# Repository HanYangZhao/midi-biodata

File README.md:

# MIDI Biodata Sonification Device

This repository was built upon code from https://github.com/electricityforprogress/BiodataFeather

Here you find the hardware and enclosure design files for the MIDI Biodata Sonification Devices

- enclosures: contains FreeCAD design and STL files for the enclosure
- firmware: 
  - MIDI_Psychogalv_328p_v021: unmodified firmware from electricityforprogress/MIDIsprout
  - arduino-nano: firmware for MIDI Biodata Sonification Device by me. This firmware offers the following new features over original version
    - Instead of menus, we use a web page to configure the device. The webpage uses webserial to send a json config to the board.
    - Allow all 7 modes of the major scale to be selected. I'm also included the chromatic and Raga Bhairav scale.
    - Selectable root note
    - Chord drone with selectable bpm and frequency. The chord is a triad based on the scale chosen.
    - Refactored code into multipe files for easier understanding.
    - Remove menu codes to save space, some optimization to free up the stack.
  - esp32: Same as main but for ESP32, the arduino-LEDFader folder needs to be copied to .../Arduino/Libraries. This firmware offer the additional:
    - 12 presets can be configured, each preset contains its own scale and root note, and can be triggered via MIDI CC/PC/NOTE
    - BLE MIDI support
- kicad: hardware design as KiCAD project and Gerber files. The board is designed to be used add-on to any microcontroller but also has footprint for the esp32s3 supermini board.

The hardware design and firmware is based on the work of electricityforprogress and thus licensed under the MIT license.

The enclosure design is however licensed under CC0 (public domain), except for the logo which is under copyright of [DipthDesign](https://www.dipth.de). For private use, anyone is free to print the enclosure with logo and without permission.

## Installation 

### Arduino nano

Download https://github.com/jgillick/arduino-LEDFader/tree/master to .../Arduino/Libraries

### ESP32

* Copy ./firmware/esp32/arduino-LEDFader to .../Arduino/Libraries
* Install arduino tiny usb library
* Device mode only support S2/S3/P4 and additional Tools menu are needed
    USB Mode=USB-OTG (TinyUSB) for S3 and P4
    USB CDC On Boot=Enabled, USB Firmware MSC On Boot=Disabled, USB DFU On Boot=Disabled
* BLE MIDI only works on ESP32-S3

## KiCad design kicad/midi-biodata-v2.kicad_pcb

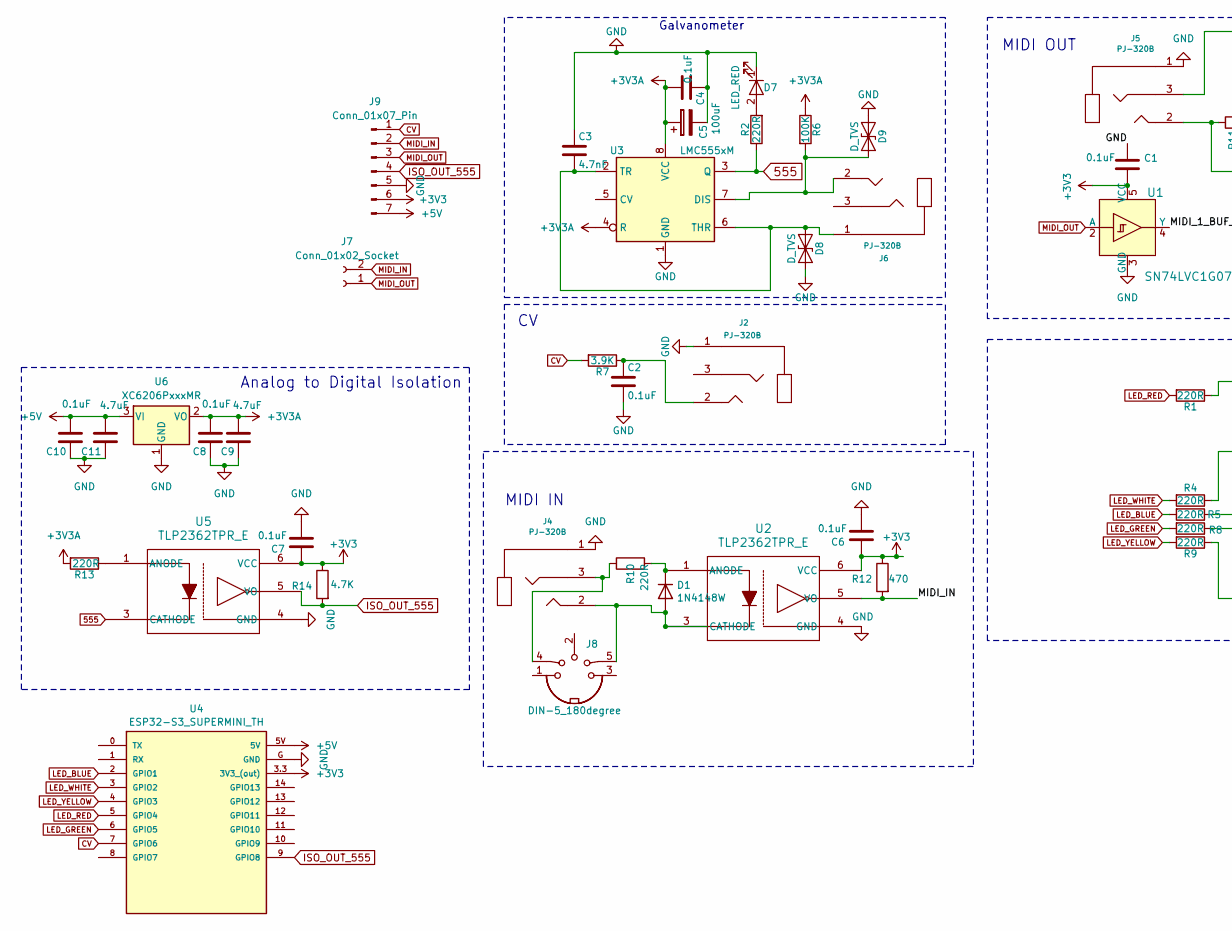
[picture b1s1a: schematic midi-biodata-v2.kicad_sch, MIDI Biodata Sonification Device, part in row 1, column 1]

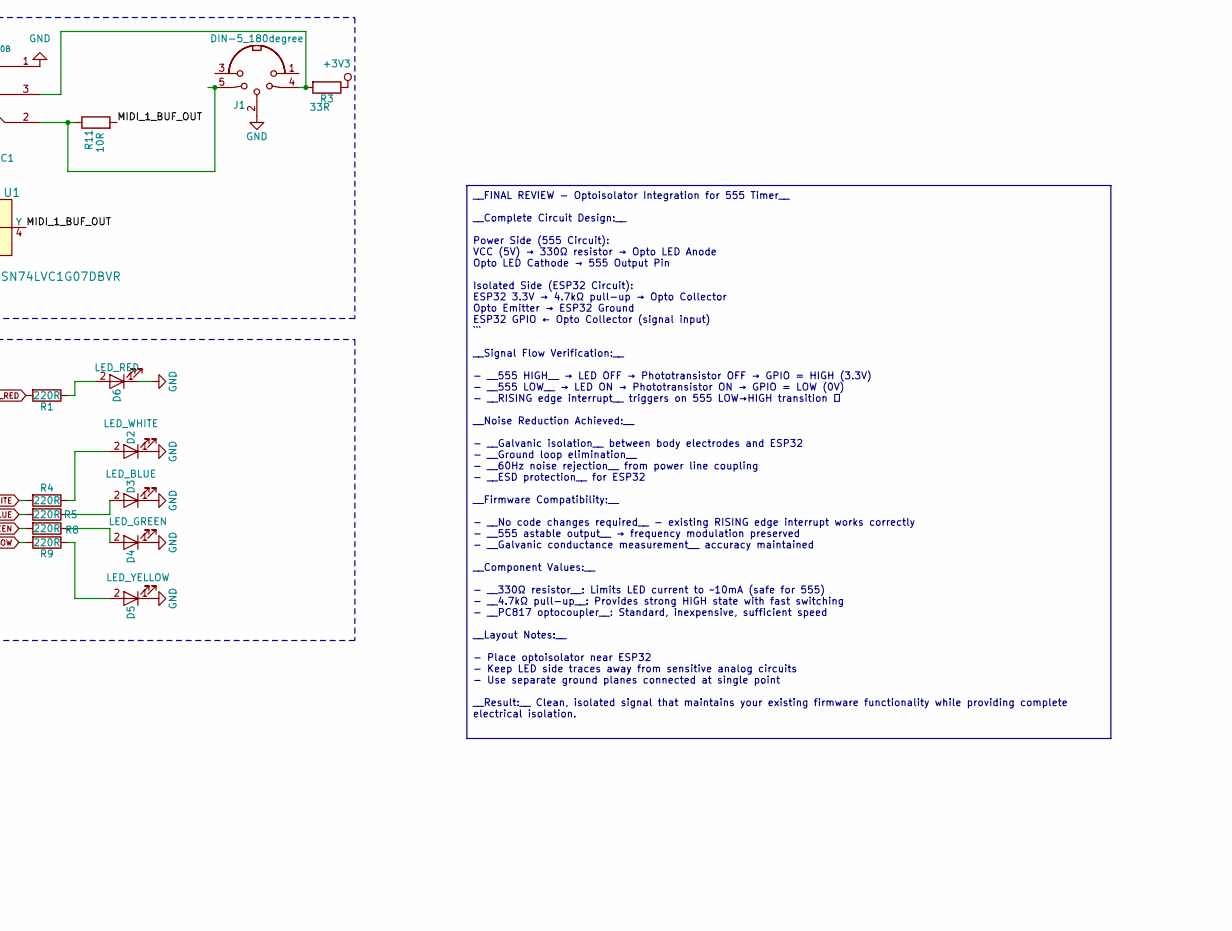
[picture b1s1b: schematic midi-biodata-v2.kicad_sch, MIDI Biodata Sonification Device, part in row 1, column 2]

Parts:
C1, C2, C4, C6, C7, C8, C10: 0.1uF; C_0402_1005Metric; LCSC C1525
C3: 4.7nF; C_0402_1005Metric; LCSC C1538
C5: 100uF; CP_Radial_D5.0mm_P2.50mm
C9, C11: 4.7uF; C_0402_1005Metric; LCSC C23733
D1: 1N4148W; D_SOD-123; LCSC C81598
D2: LED_WHITE; D_0603_1608Metric_Pad1.05x0.95mm_HandSolder; LCSC C2290
D3: LED_BLUE; D_0805_2012Metric_Pad1.15x1.40mm_HandSolder; LCSC C34499
D4: LED_GREEN; D_0805_2012Metric_Pad1.15x1.40mm_HandSolder; LCSC C2297
D5: LED_YELLOW; D_0805_2012Metric_Pad1.15x1.40mm_HandSolder; LCSC C2296
D6, D7: LED_RED; D_0603_1608Metric_Pad1.05x0.95mm_HandSolder; LCSC C2286
D8, D9: D_TVS; D_SOD-882; LCSC C294611
J1, J8: DIN-5_180degree; DIN-5-MIDI-JACK
J2, J4, J5, J6: PJ-320B; 3.5mm_stereo_jack_PJ320B_THRU; LCSC C2884998
J7: Conn_01x02_Socket; PinHeader_1x02_P2.54mm_Vertical
J9: Conn_01x07_Pin; PinHeader_1x07_P2.54mm_Vertical
R1, R2, R4, R5, R8, R9, R10, R13: 220R; R_0402_1005Metric; LCSC C25091
R3: 33R; R_0402_1005Metric; LCSC C25105
R6: 100K; R_0402_1005Metric; LCSC C25741
R7: 3.9K; R_0805_2012Metric; LCSC C17614
R11: 10R; R_0402_1005Metric; LCSC C25077
R12: 470; R_0805_2012Metric; LCSC C17710
R14: 4.7K; R_0805_2012Metric; LCSC C17710
U1: SN74LVC1G07DBVR; SOT-23-5; Digi-Key_PN 296-8485-1-ND
U2, U5: TLP2362TPR_E; tlp2362; LCSC C37658
U3: LMC555xM; DIP-8_W7.62mm
U4: ESP32-S3_SUPERMINI_TH; MODULE_ESP32-C3_SUPERMINI_TH
U6: XC6206PxxxMR; SOT-23-3

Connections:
555: R2.1, U3.3 (Q), U5.3 (CATHODE)
+3V3: C1.2, C6.1, C7.1, J9.6, R3.1, R12.1, R14.1, U1.5 (VCC), U2.6 (VCC), U4.3.3 (3V3_(out)), U5.6 (VCC)
+3V3A: C4.2, C5.1, C8.2, C9.2, R6.1, R13.2, U3.4 (R), U3.8 (VCC), U6.2 (VO)
+5V: C10.2, C11.2, J9.7, U4.5V, U6.3 (VI)
/MIDI_1_BUF_OUT: R11.2, U1.4 (Y)
CV: J9.1, R7.2, U4.7 (GPIO6)
GND: C1.1, C2.2, C3.1, C4.1, C5.2, C6.2, C7.2, C8.1, C9.1, C10.1, C11.1, D2.1 (K), D3.1 (K), D4.1 (K), D5.1 (K), D6.1 (K), D7.1 (K), D8.2 (A2), D9.1 (A1), J1.2, J2.1, J4.1, J5.1, J9.5, U1.3 (GND), U2.4 (GND), U3.1 (GND), U4.G (GND), U5.4 (GND), U6.1 (GND)
ISO_OUT_555: J9.4, R14.2, U4.9 (GPIO8), U5.5 (VO)
LED_BLUE: R5.2, U4.2 (GPIO1)
LED_GREEN: R8.2, U4.6 (GPIO5)
LED_RED: R1.2, U4.5 (GPIO4)
LED_WHITE: R4.2, U4.3 (GPIO2)
LED_YELLOW: R9.2, U4.4 (GPIO3)
MIDI_IN: J7.2, J9.2, R12.2, U2.5 (VO)
MIDI_OUT: J7.1, J9.3, U1.2 (A)
unnamed: C2.1, J2.2, R7.1
unnamed: D1.2 (A), J4.2, J8.5, U2.3 (CATHODE)
unnamed: D1.1 (K), R10.2, U2.1 (ANODE)
unnamed: D2.2 (A), R4.1
unnamed: D3.2 (A), R5.1
unnamed: D4.2 (A), R8.1
unnamed: D5.2 (A), R9.1
unnamed: D6.2 (A), R1.1
unnamed: D7.2 (A), R2.2
unnamed: C3.2, D8.1 (A1), J6.1, U3.2 (TR), U3.6 (THR)
unnamed: D9.2 (A2), J6.2, R6.2, U3.7 (DIS)
unnamed: J1.4, J5.3, R3.2
unnamed: J1.5, J5.2, R11.1
unnamed: J4.3, J8.4, R10.1
unnamed: R13.1, U5.1 (ANODE)

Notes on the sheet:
__FINAL REVIEW - Optoisolator Integration for 555 Timer__ __Complete Circuit Design:__ Power Side (555 Circuit): VCC (5V) → 330Ω resistor → Opto LED Anode Opto LED Cathode → 555 Output Pin Isolated Side (ESP32 Circuit): ESP32 3.3V → 4.7kΩ pull-up → Opto Collector Opto Emitter → ESP32 Ground ESP32 G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
Galvanometer
MIDI IN
Analog to Digital Isolation
MIDI OUT

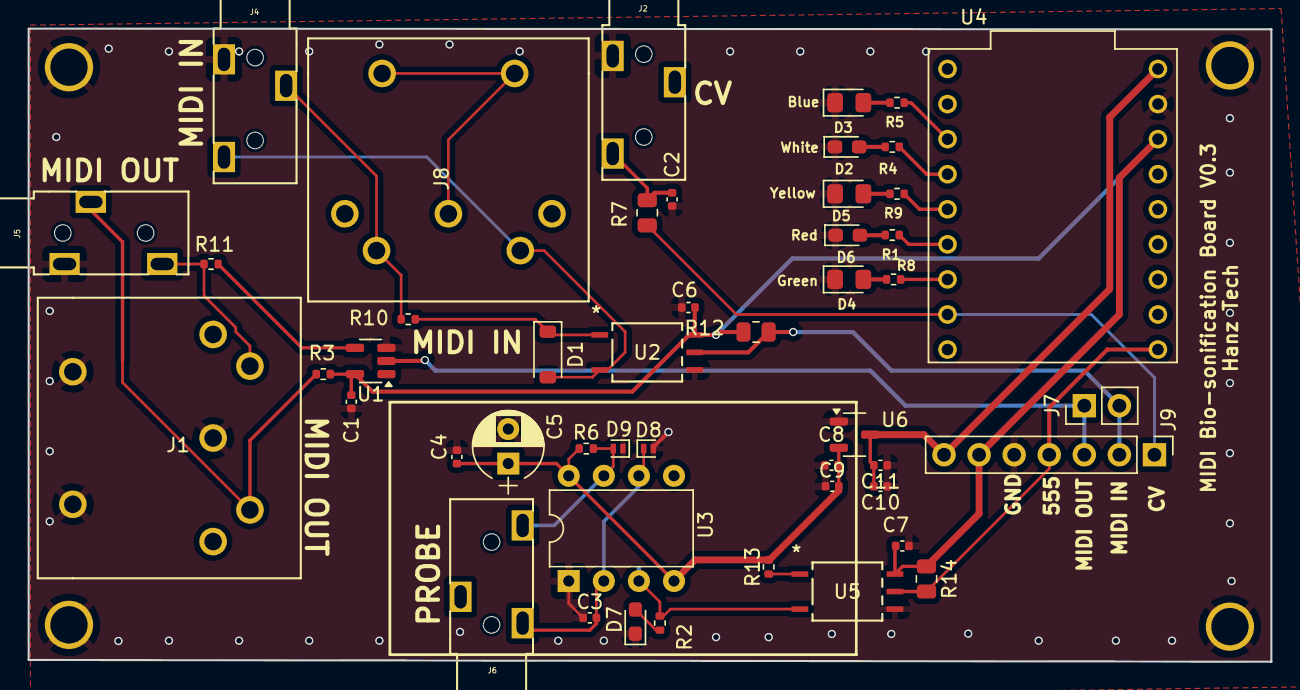
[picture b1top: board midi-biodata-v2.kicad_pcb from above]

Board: 2 copper layers, 90.0 x 45.8 mm, 48 parts (0 on the bottom side), 30 nets.

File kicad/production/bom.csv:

Designator,Footprint,Quantity,Value,LCSC Part #
"_4, _3, _2, ",Fiducial_1mm_Dia_2.54mm_Outer_CopperTop,4,Fiducial_1mm_Dia_2.54mm_Outer_CopperTop,
"C1, C2, C4, C6",0402,4,0.1uF, C1525
C3,0402,1,4.7nF,C1538
C5,CP_Radial_D5.0mm_P2.50mm,1,100uF,
D1,D_SOD-123,1,1N4148W,    C81598
D2,0603,1,LED_WHITE,C2290
D3,0805,1,LED_BLUE,C34499
D4,0805,1,LED_GREEN,C2297
D5,0805,1,LED_YELLOW,C2296
"D6, D7",0603,2,LED_RED,C2286
"D8, D9",D_SOD-882,2,D_TVS,C294611
"J1, J8",DIN-5-MIDI-JACK,2,DIN-5_180degree,
J3,PinHeader_1x13_P2.54mm_Vertical,1,Conn_01x14_Pin,
J7,PinHeader_1x02_P2.54mm_Vertical,1,Conn_01x02_Socket,
"R1, R10, R11, R2, R3, R4, R5, R8, R9",0402,9,220R,C25091
R12,0805,1,470,C17710 
R6,0402,1,100K,C25741
R7,0805,1,3.9K,C17614
U1,SOT-23-5,1,SN74LVC1G07DBVR,C7829
U2,tlp2362,1,TLP2362TPR_E,C37658
U3,DIP-8_W7.62mm,1,LMC555xM,
U4,MODULE_ESP32-C3_SUPERMINI_TH,1,ESP32-S3_SUPERMINI_TH,

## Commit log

2025-05-13 Removed MCU from board, added proper midi out
2025-05-13 send to jlcpcb
2025-05-27 added updated firmware
2025-05-27 fixed midi routing on the pcb board
2025-05-27 refactored code into multiple files (thx chatgpt)
2025-05-27 add music modes, add feature to set root note
2025-05-28 Fixed note scaling, fixed web configurator
2025-05-29 fixed duplicate root note, cleaned up code to save memory, added droning chord feature
2025-05-29 Updated docs
2025-05-29 Update docs again
2025-05-29 Update web_serial_config.html with min and max threshold
2025-05-29 updated drone velocity, otimized code for ram space
2025-06-01 add support for esp32
2025-06-01 revert some files
2025-06-01 cleanup
2025-06-01 Add LEDFader for esp32
2025-06-03 Add support for usb midi on esp32s2
2025-06-04 Added BLE, fixed MIDI cc
2025-06-04 fix cc again
2025-06-04 fixed ble
2025-06-05 add support for preset via midi cc and midi pc
2025-06-05 add drone chord quality
2025-06-05 add drone velocity
2025-06-05 add free drone and bpm drone mode
2025-06-05 added midi note trigger for presets
2025-06-08 minor cleanup
2025-06-09 added more chord options
2025-06-09 add pentatonic scales
2025-06-09 Download and upload json files
2025-06-09 Restrict preset change signal to global midi channel
2025-06-09 add firmware version in web ui, fix midi handling on cc and program change
2025-06-09 fix midi channel
2025-06-09 update dashboard, add midi input channel
2025-06-12 move website
2025-06-12 move website to root folder
2025-06-14 Increase to 12 presets
2025-06-14 Lower threshold to 1.00 on website
2025-06-14 bump to 1.1.0
2025-06-28 cleanup, changed footprint for 3.5mm jack
2025-06-29 Add esp32s2 supermini board
2025-06-30 updated board with esp32 s3 mini integration
2025-06-30 fixed esp32s3 board
2025-07-02 Fix BLE midi support for esp32s3
2025-07-02 update docs
2025-07-02 send v0.2 to production
2025-08-01 add notes for optoisolator placement
2025-08-02 update board to 0.3, add analog partition to board
